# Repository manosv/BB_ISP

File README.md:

BB_ISP
======

Breadboard ISP adapter for 8 pin DIP ATtiny. This goes directly on top of the device on a breadboard and allows easy in circuit programming.
Should be compatible to: ATtiny 13, ATtiny 22 (90s2343),ATtiny 25, ATtiny 45 and ATtiny 85.

Inspired by [this](http://www.adafruit.com/product/1465).

Update: Boards arrived from OSH Park. See below for photos of the prototype.

[Shared Project at OSH Park](http://oshpark.com/shared_projects/9qCTtAzD)

PCB render front

PCB render rear

The prototype in all its glory

The prototype on a breadboard on top of a ATtiny 22

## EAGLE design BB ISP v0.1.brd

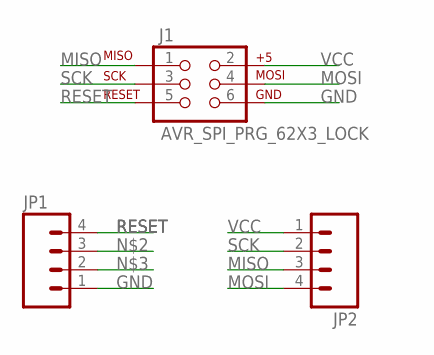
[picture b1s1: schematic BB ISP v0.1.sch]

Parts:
J1: AVR_SPI_PRG_62X3_LOCK; 2X3_LOCK
JP1, JP2: M04PTH; 1X04

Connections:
GND: J1.6, JP1.1
MISO: J1.1, JP2.3
MOSI: J1.4, JP2.4
RESET: J1.5, JP1.4
SCK: J1.3, JP2.2
VCC: J1.2, JP2.1

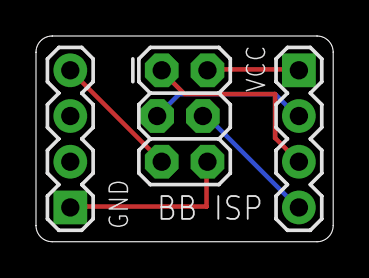
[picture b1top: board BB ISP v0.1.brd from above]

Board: 2 copper layers, 16.5 x 11.4 mm, 3 parts (0 on the bottom side), 6 nets.

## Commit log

2013-08-08 Initial release
2013-08-25 Photos of prototype
2013-08-25 added photos of prototype build

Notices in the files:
parts and their libraries:
SparkFun-Connectors: Licensing: CC v3.0 Share-Alike You are welcome to use this library for commercial purposes.
